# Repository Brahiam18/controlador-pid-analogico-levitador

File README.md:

# Controlador PID analógico para levitación electromagnética

-brightgreen)

Diseño, cálculo, simulación, implementación y pruebas de un controlador **PID 100 % analógico**, construido solo con amplificadores operacionales LM741, para estabilizar la posición de un objeto en levitación por atracción electromagnética. El repositorio incluye el informe técnico completo (PDF y código fuente LaTeX), las figuras, la lista de materiales, las mediciones del montaje físico y su comparación con la teoría.

> **TL;DR (EN):** Fully analog, parallel PID controller built with LM741 op-amps for an electromagnetic levitation system: error amplifier, P / I (with anti-windup leak) / D (with high-frequency limiting) stages, and a summing stage with offset that produces a 1–3 V control signal. Reference voltages are generated by resistive dividers isolated with voltage-follower buffers. Includes hand calculations, Proteus simulation and an IEEE-style report written in LaTeX (Spanish).

📄 **Informe:** [`informe/Informe_PID_Analogico_Levitador.pdf`](informe/Informe_PID_Analogico_Levitador.pdf)

---

## Resumen del diseño

| Parámetro | Valor |
|---|---|
| Topología | PID en **paralelo** (P, I y D independientes; no en cascada) |
| Amplificadores | 7 × LM741 (U1–U7) |
| Alimentación de diseño | ±16 V |
| Salida del controlador | 1 V a 3 V (1 V = error nulo) |
| Referencia de posición | `V_ref` ≈ 2 V |
| Ganancias finales | `Kp = 2.2` · `Ki,max = 4.5` · `Kd,max = 22` |
| Frecuencias de diseño | integrador: `f_aw ≈ 0.2 Hz` · derivador: `f_c ≈ 150 Hz` |

**¿Por qué un PID?** Un levitador por atracción es inestable en lazo abierto (teorema de Earnshaw). Se descartaron el control todo-o-nada (fuerza discontinua), el P puro y el PD (ambos dejan error de estado estable o no lo eliminan) y se eligió el PID: P corrige el error instantáneo, I elimina el error de estado estable y D aporta el amortiguamiento que el sistema no tiene por sí mismo.

## Arquitectura

```mermaid
flowchart LR
    S["Sensor de posición<br/>V_sensor"] --> D["Diferenciador de error<br/>U1"]
    VR["Divisor + buffer V_ref<br/>R12, R13, U6"] --> D
    D -- "V_e" --> P["Proporcional<br/>U2 (Pot1, R5)"]
    D -- "V_e" --> I["Integral + anti-windup<br/>U3 (Pot2, Ci, R11)"]
    D -- "V_e" --> De["Derivativo + filtro<br/>U4 (R6, C2, Pot3)"]
    P --> SUM["Sumador<br/>U5 (R7–R10, R_offset)"]
    I --> SUM
    De --> SUM
    VO["Divisor + buffer V_off<br/>R14, R15, U7"] --> SUM
    SUM -- "1 a 3 V" --> OUT["Etapa de potencia y bobina"]
    OUT --> OBJ["Posición del objeto"]
    OBJ -. "realimentación" .-> S
```

| Etapa | CI | Ecuación de diseño | Valores finales |
|---|---|---|---|
| Diferenciador de error | U1 | `V_e = (R2/R1)·(V_sensor − V_ref)`, `Av = 1` | R1 = R2 = R3 = R4 = 10 kΩ |
| Proporcional (P) | U2 | `V_P = −(Pot1/R5)·V_e` | R5 = 10 kΩ, Pot1 = 22 kΩ (`Kp = 2.2`) |
| Integral (I) | U3 | `V_I = −(1/(Pot2·Ci))∫V_e dt`, con fuga `R11 ‖ Ci`: `K_max = R11/Pot2` | Pot2 = 220 kΩ, Ci = 1 µF, R11 = 1 MΩ (`K_max = 4.5`) |
| Derivativo (D) | U4 | `V_D = −Pot3·C2·dV_e/dt`, `G_max = Pot3/R6`, `f_c = 1/(2π·R6·C2)` | R6 = 1 kΩ, C2 = 1 µF, Pot3 = 22 kΩ (`Kd,max = 22`) |
| Sumador | U5 | `V_PID = −(R10/R7·V_P + R10/R8·V_I + R10/R9·V_D + R10/R_offset·V_off)` | R7 = R8 = R9 = R_offset = 10 kΩ, R10 = 1 kΩ (ganancia 0.1 por rama) |
| Referencia `V_ref` | U6 | divisor + seguidor | R12 = 160 kΩ, R13 = 240 kΩ (desde 5 V → 2 V) |
| Offset `V_off` | U7 | divisor + seguidor | R14 = 96 kΩ (calculada; **pendiente de medir**), R15 = 160 kΩ |

La nomenclatura de las resistencias fue actualizada respecto a la primera versión del informe; la tabla de equivalencias está en [`docs/nomenclatura.md`](docs/nomenclatura.md).

## Problemas encontrados y cómo se resolvieron

1. **Saturación del sumador.** Con ganancia unitaria por rama, la salida teórica ante error máximo era de 23.24 V, muy por encima de los rieles. Se bajó la ganancia por rama a 0.1 (`R10`: 10 kΩ → 1 kΩ), se agregó un voltaje de offset para fijar el piso en 1 V y se redujo `Kp` de 3 a 2.2 para que el máximo converja a ≈ 3 V (3.02 V).
2. **Topología del integrador.** La resistencia de anti-windup se había conectado *en serie* con el capacitor, dejando la realimentación abierta en continua. Al colocarla en **paralelo** (`R11 ‖ Ci`) el integrador recuperó su comportamiento (salida nula para error nulo, rampa ante un escalón). Además se rediseñó `Ki` (ganancia DC máxima de 80 → 4.5) porque la original saturaba ante errores pequeños.
3. **Efecto de carga en los divisores.** Los divisores de `V_ref` y `V_off` entregaban menos voltaje del calculado al conectarse a la etapa siguiente. Se intercaló un seguidor de voltaje (U6 y U7) en cada uno.

## Placa de circuito impreso (2 PID con etapa de potencia por tarjeta)

En [`hardware/pcb/`](hardware/pcb/) hay una placa de una sola cara (170.2 × 116.8 mm, cabe en una baquela de 20 × 20 cm) con **dos controladores PID independientes, cada uno con su etapa de potencia** (TIP122, banco de sensado de 3 × 1 Ω y bornes de bobina). Para los cuatro controladores se hacen **dos tarjetas iguales**. Está lista para quemar en baquela: archivos EAGLE para Fusion, hojas de cobre espejado a escala 1:1 y de ensamble con los nombres de cada pieza (U1 a U8 sobre los TL074CN), lista de puentes y el generador en Python. El informe todavía describe el diseño con LM741.

## Etapa de potencia (convertidor tensión-corriente)

La salida del PID (`V_PID`, 1 V a 3 V) no mueve la bobina directamente: pasa por un **convertidor tensión-corriente** con un amplificador operacional (U8) y un transistor Darlington TIP122, de modo que la bobina recibe una **corriente proporcional a `V_PID`** y no depende de su resistencia ni de la fuente (mientras el transistor no se sature). Es lo que se necesita en un levitador: la fuerza magnética depende de la corriente.

**Cómo funciona.**

1. `V_PID` llega a la entrada no inversora de U8 por `R17` (10 kΩ), el potenciómetro de calibración `POT4` (10 kΩ) y `R16` (270 Ω); `POT4` fija cuántos amperios se obtienen por voltio de `V_PID`.
2. U8 maneja la base del TIP122 a través de `R_BASE` (270 Ω) y del diodo `D2` (1N4148).
3. La corriente de la bobina pasa por el TIP122 y por el **banco de sensado** (3 × 1 Ω / 5 W en paralelo = 0.33 Ω), cuya caída `V_ISENSE = 0.33 V/A · I` vuelve a la entrada inversora de U8 por `R18` (1 kΩ).
4. U8 corrige la base hasta que `V_ISENSE` iguala la tensión de su entrada no inversora; por eso `I ≈ V₊ / R_sense`, es decir, **la corriente sigue a `V_PID`**.
5. `D1` (1N5408) en antiparalelo con la bobina absorbe la tensión inducida cuando se corta la corriente. `C3` (10 nF, opcional) compensa el lazo de U8 si oscila.

| Elemento | Valor | Función |
|---|---|---|
| `R17` | 10 kΩ | entrada del convertidor desde `V_PID` |
| `POT4` | 10 kΩ | calibración (A por voltio de `V_PID`) |
| `R16` | 270 Ω | protección de la entrada no inversora de U8 |
| `R18` | 1 kΩ | realimentación de `V_ISENSE` a la entrada inversora |
| `R_BASE` | 270 Ω | limita la corriente de base del TIP122 |
| `R_sense` | 3 × 1 Ω / 5 W (0.33 Ω) | sensado de la corriente de la bobina |
| `D1` / `D2` | 1N5408 / 1N4148 | protección de la bobina / protección de la base |
| TIP122 | Darlington NPN | elemento de paso (≈ 4.7 W con 1 A: lleva disipador de ≤ 10 °C/W y tab aislado) |

**Simulación (Proteus).** El archivo [`simulacion/proteus/EtapaPID1.pdsprj`](simulacion/proteus/EtapaPID1.pdsprj) contiene el PID completo con esta etapa. La captura muestra una **variante de simulación** para comprobar el principio: LM741 como U8, resistencia de sensado de 1 Ω / 10 W, bobina de 6 Ω y fuente de 24 V. Con `V₊ = 3.015 V` la corriente por el TIP122 es de **3.014 A**, igual a `V₊ / 1 Ω`: el convertidor entrega la corriente que se le pide. En el montaje real el sensado es de 0.33 Ω, la bobina ronda los 4 Ω y la corriente de trabajo es de unos 1 A, alimentada desde módulos reductores (ver [`docs/estado_del_proyecto.md`](docs/estado_del_proyecto.md)).

## Simulación en Proteus

Cada etapa se simuló y midió con voltímetros virtuales antes del montaje. El proyecto de Proteus se encuentra en [`simulacion/proteus/`](simulacion/proteus/) (`EtapaPID1.pdsprj`). El esquemático completo está en [`informe/figuras/proteus_circuito_completo.png`](informe/figuras/proteus_circuito_completo.png) y el esquemático hecho a mano en [`informe/figuras/circuito_manuscrito.jpeg`](informe/figuras/circuito_manuscrito.jpeg).

## Resultados experimentales

Voltaje teórico vs. práctico por etapa, para error mínimo, medio y máximo (`V_sensor` = 0, 2 y 5 V con `V_ref` = 2 V). Las mediciones se tomaron con multímetro sobre el montaje en protoboard alimentado a ±16 V. Los datos completos, con error absoluto y relativo, están en [`datos/mediciones_practicas.csv`](datos/mediciones_practicas.csv).

| Etapa | Teórico mín. (V) | Teórico medio (V) | Teórico máx. (V) | Práctico mín. (V) | Práctico medio (V) | Práctico máx. (V) |
|---|---:|---:|---:|---:|---:|---:|
| Diferenciador | −2 | 0 | 3 | −2.02 | 0 | 2.99 |
| Proporcional (P) | 4.38 | −0.01 | −6.6 | 4.46 | −0.15 | −6.6 |
| Integral (I) | 9.14 | 0.07 | −13.5 | 6.22 | −0.32 | −13.22 |
| Derivativo (D) | −3.24 mV | −3.24 mV | −3.3 mV | 3 mV | 3 mV | 172 mV |
| Sumador | −0.35 | 1 | 3.01 | −0.04 | 1 | 2.96 |
| Divisor `V_ref` | 2 | 2 | 2 | 2 | 2 | 2 |
| Divisor `V_off` | −10.1 | −10.1 | −10.1 | −10.21 | −10.21 | −10.21 |

**Lectura rápida:**
- El diferenciador, el proporcional, el sumador y los divisores con buffer coinciden con lo calculado (error relativo ≤ 2 % donde el valor teórico es mayor que 0.5 V). La salida del sumador con error máximo es 2.96 V, dentro del rango de diseño de 1 V a 3 V, y con error medio es exactamente 1 V.
- La etapa integral con error mínimo da 6.22 V frente a 9.14 V teóricos (−32 %). Con ese valor práctico, el sumador resulta en −0.04 V, que es coherente con la salida medida.
- En la etapa derivativa, con entrada en DC, los valores son del orden de milivoltios; el de 172 mV con error máximo queda pendiente de analizar.

### Montaje físico

| Circuito en protoboard | Medición a la salida del diferenciador (2.99 V) |
|:-:|:-:|
|  |  |

## Simulación del campo y póster

Modelo del campo magnético de las 4 bobinas y del imán (aproximación de dipolos, solvers propios en Python, no FEMM) para estimar la corriente de equilibrio: unos **0,7 A por bobina a 30 mm** (±15 %). Es una estimación ilustrativa; **la levitación todavía no se ha logrado en el montaje**.

<p align="center">
  
</p>

- Video (720p): [`docs/simulacion_campo/campo_levitador_720p.mp4`](docs/simulacion_campo/campo_levitador_720p.mp4)
- Visor interactivo 3D: [`docs/simulacion_campo/campo_levitador.html`](docs/simulacion_campo/campo_levitador.html) (descargar y abrir en el navegador)
- Notas del modelo: [`docs/simulacion_campo/README.md`](docs/simulacion_campo/README.md)
- Póster presentado en METIE 2026: [PDF](docs/poster_metie/Poster_Levitador_METIE.pdf) · [PPTX](docs/poster_metie/Poster_Levitador_METIE.pptx)

<p align="center">
  
</p>

## Estructura del repositorio

```text
.
├── informe/
│   ├── informe_pid_analogico.tex        # código fuente del informe (IEEEtran)
│   ├── Informe_PID_Analogico_Levitador.pdf
│   └── figuras/                         # esquemáticos (incl. Proteus de la etapa de potencia), cálculos a mano y diagrama de bloques
│       └── pruebas/                     # fotografías del montaje y de las mediciones
├── docs/
│   ├── nomenclatura.md                  # nomenclatura vigente y equivalencias con la versión anterior
│   ├── errata-y-pendientes.md           # inconsistencias detectadas en el informe y tareas abiertas
│   ├── estado_del_proyecto.md           # estado actual, qué falta y requisitos de alimentación
│   ├── plan_2027.md                     # plan para lograr la levitación estable
│   ├── guia_depuracion.md               # diagnósticos y pruebas de un PID
│   ├── resumen_para_posgrado.md         # resumen del proyecto (ES/EN)
│   ├── simulacion_campo/                # visualización interactiva del campo y video
│   └── poster_metie/                    # póster de la muestra METIE 2026
├── hardware/
│   ├── lista_de_materiales.md
│   ├── lista_de_materiales.csv
│   └── pcb/                             # placa de 2 PID: .sch/.brd (Fusion/EAGLE), PDF de cobre y ensamble, generador
├── simulacion/
│   └── proteus/                         # proyecto de Proteus (PID + etapa de potencia)
├── pruebas/
│   ├── montaje/                         # fotos del montaje de los 4 PID con la base 3D (nov. 2026)
│   └── levitacion/                      # fotos de los 4 PID levitando y Vref por altura (pendiente)
├── datos/
│   └── mediciones_practicas.csv         # teórico vs. práctico, con error absoluto y relativo
├── fuente/                              # fuente ±16 V (1,5 A) / +5 V de los 4 PID (informe, esquemáticos, simulación, PCB, pruebas)
├── LICENSE
└── README.md
```

## Compilar el informe

Requiere una distribución de TeX Live con `IEEEtran`, `siunitx` y `booktabs`.

```bash
cd informe
latexmk -pdf informe_pid_analogico.tex
```

## Estado y próximos pasos

**Noviembre de 2026:** los 4 PID, la etapa de potencia y la base impresa en 3D están montados y funcionando por separado, pero la levitación estable a 3 cm quedó pendiente: falta un método rápido para fijar los `V_ref` y los sensores ven una variación muy pequeña del campo. El trabajo continúa en 2027; ver [`docs/estado_del_proyecto.md`](docs/estado_del_proyecto.md), [`docs/plan_2027.md`](docs/plan_2027.md) y [`docs/guia_depuracion.md`](docs/guia_depuracion.md).

- [x] Diseño y cálculo de cada etapa
- [x] Simulación en Proteus
- [x] Informe técnico en LaTeX (formato IEEE)
- [ ] Medir `R14` (divisor de `V_off`) y registrar su valor final
- [x] Tomas de voltaje prácticas por etapa (error mínimo, medio y máximo)
- [x] Fotografías del montaje
- [ ] Analizar la desviación de la etapa integral con error mínimo y el valor de la etapa derivativa con error máximo
- [ ] Capturas de osciloscopio con la escala legible (pruebas con señal senoidal)
- [x] Agregar el archivo del proyecto de Proteus
- [x] Documentar la etapa de potencia (README e informe)
- [ ] Fotos de los 4 PID con el objeto levitando y `V_ref` por altura ([`pruebas/levitacion/`](pruebas/levitacion/))
- [ ] Aplicar la [errata](docs/errata-y-pendientes.md) al informe (versión 1.1)

## Autor

**Brahiam Alberto Campiño Romero**: Ingeniería Electrónica, Universidad de Ibagué (Ibagué-Tolima, Colombia) · [@Brahiam18](https://github.com/Brahiam18)

## Licencia

[MIT](LICENSE)

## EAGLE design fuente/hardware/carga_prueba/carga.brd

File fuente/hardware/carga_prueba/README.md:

# Placa de la carga de prueba R_L (10 Ω / 20 Ω)

Placa de **una cara** de **95 × 95 mm** para las 4 resistencias de cemento de **10 Ω / 10 W** de la carga de prueba. No uses la protoboard para esto: sus contactos aguantan alrededor de 1 A y las resistencias pasan de 150 °C.

## Circuito
(R1 + R2) ‖ (R3 + R4). **JP1** es una bornera de 2 vías que elige la carga:

| JP1 | Resistencia | Corriente con 16 V | Potencia en cada resistencia |
|---|---|---|---|
| **Puenteado** (alambre de 18 AWG o interruptor de 3 A) | 10 Ω | **1,6 A** (corriente completa) | 6,4 W |
| **Abierto** | 20 Ω (solo R1 + R2) | **0,8 A** (media corriente) | 6,4 W en R1 y R2; R3 y R4 frías |

**J1** (bornera de 2 vías) va con un cable de 18 AWG a **J4** (+16 V / GND) o a **J5** (−16 V / GND) de la fuente. La polaridad no importa.

## Archivos
| Archivo | Para qué sirve |
|---|---|
| `cobre_espejado_1a1.pdf` | Cara de cobre espejada a 1:1 para planchar (la regla debe medir 50 mm) |
| `ensamble_1a1.pdf` | Lado de componentes a 1:1 |
| `carga.sch`, `carga.brd` | Formato EAGLE para Fusion (cargar los dos juntos) |
| `generar.py` | Genera todo lo anterior (`python3 generar.py`) |

## Reglas y montaje
- Pistas de 2,5 mm con quiebres a 45°; separación mínima entre redes de 1,75 mm; ninguna pista a menos de 2 mm del borde.
- Pads de 3,2 mm con taladro de 1,2 mm para las patas de las resistencias (55,88 mm entre agujeros) y de 1,3 mm para las borneras.
- **Monta las resistencias levantadas 5–10 mm** de la placa, con las patas dobladas en ángulo recto. Quedan separadas unos 9 mm entre sí para que se ventilen.
- Estaña las pistas.
- Pon separadores M3 en los 4 agujeros para que la placa no quede apoyada sobre la mesa.
- **No las toques durante la prueba** y espera a que se enfríen antes de cambiar el puente.

## Materiales
| Cant. | Pieza |
|---|---|
| 4 | Resistencia de cemento 10 Ω / 10 W |
| 2 | Bornera de tornillo 2 vías, paso 5,08 mm (J1, JP1) |
| 1 | Baquela una cara 10 × 10 cm |
| 4 | Separadores M3 de 10 mm con tornillo |
| — | Cable de 18 AWG para la conexión a la fuente y para el puente de JP1 |

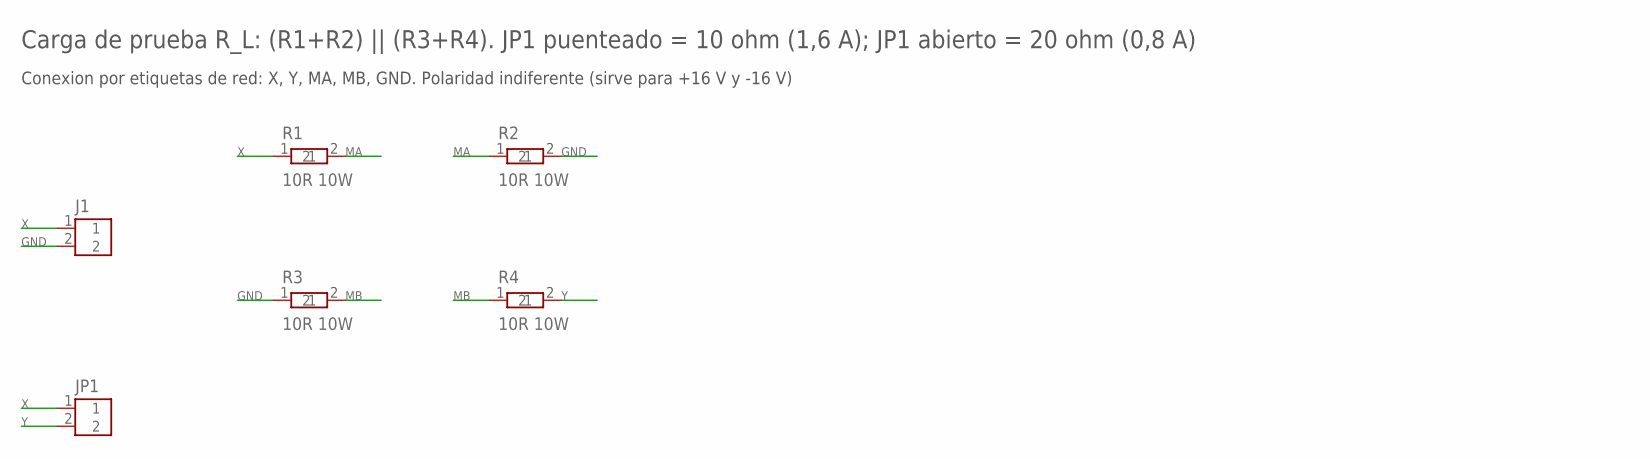
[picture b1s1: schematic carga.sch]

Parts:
J1: A J4 o J5; TERM2
JP1: SEL 10/20R; TERM2
R1, R2, R3, R4: 10R 10W; R10W

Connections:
GND: J1.2, R2.2, R3.1
MA: R1.2, R2.1
MB: R3.2, R4.1
X: J1.1, JP1.1, R1.1
Y: JP1.2, R4.2

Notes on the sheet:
Carga de prueba R_L: (R1+R2) || (R3+R4). JP1 puenteado = 10 ohm (1,6 A); JP1 abierto = 20 ohm (0,8 A)
Conexion por etiquetas de red: X, Y, MA, MB, GND. Polaridad indiferente (sirve para +16 V y -16 V)

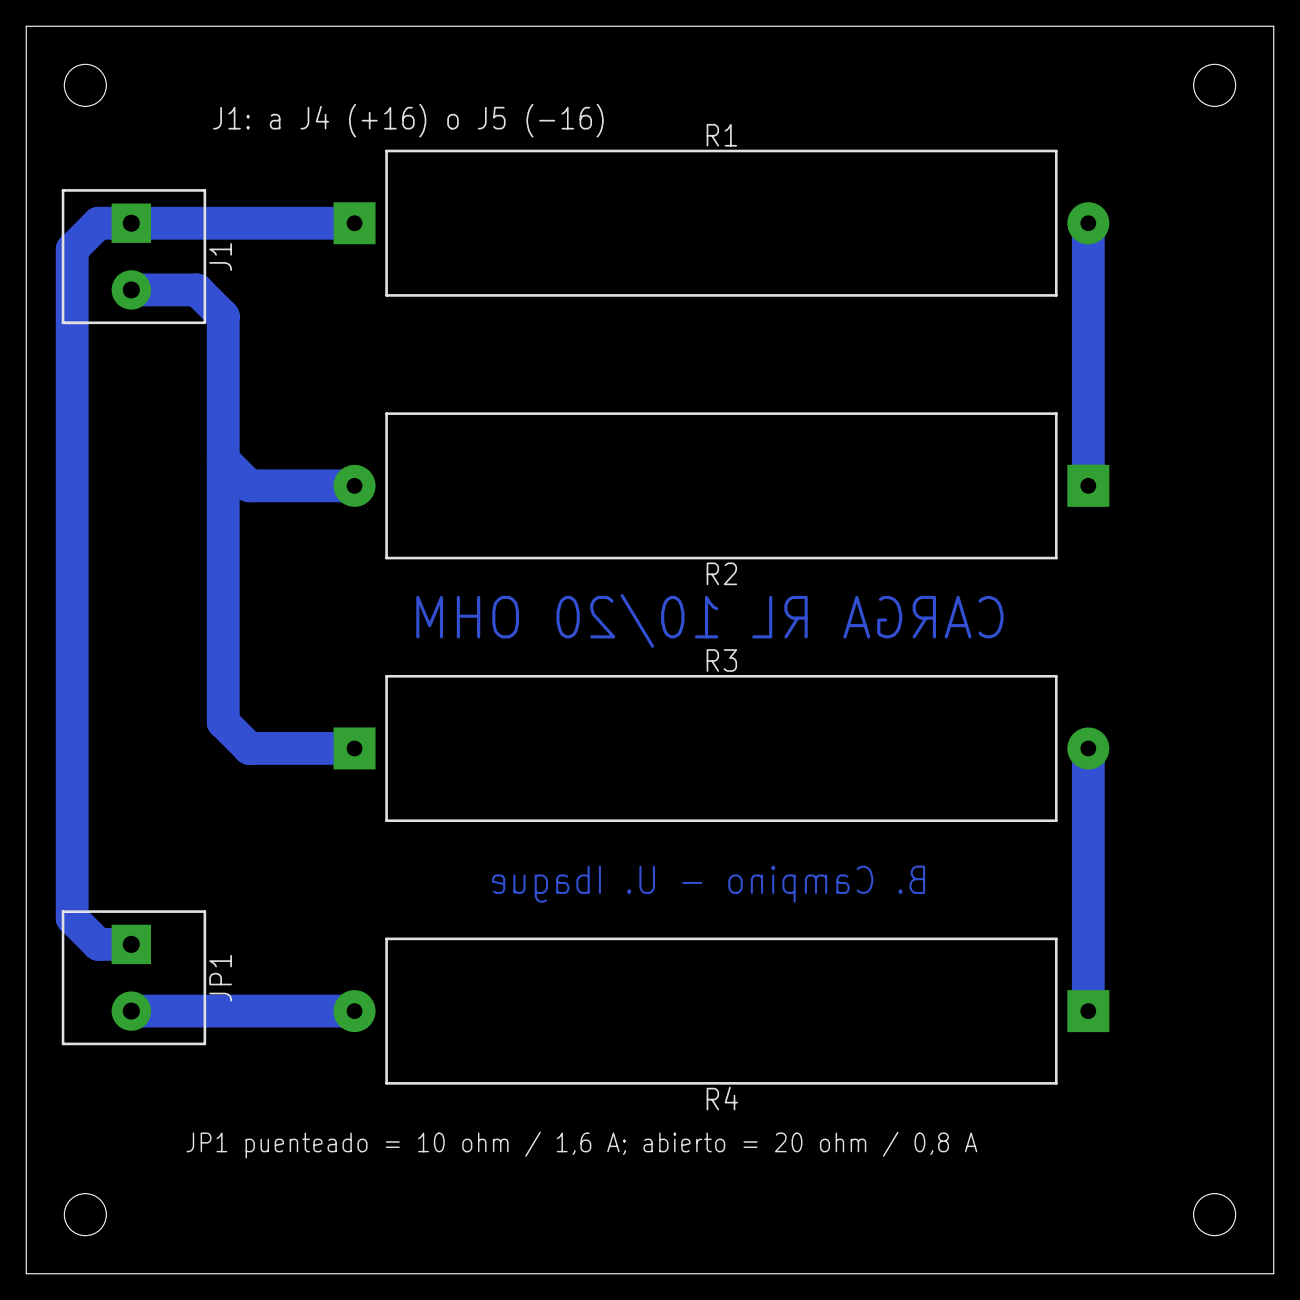
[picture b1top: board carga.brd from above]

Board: 2 copper layers, 95.0 x 95.0 mm, 6 parts (0 on the bottom side), 5 nets.

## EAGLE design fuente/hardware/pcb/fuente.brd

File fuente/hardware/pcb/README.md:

# Placa de la fuente ±16 V / 1,6 A y +5 V (versión 2.2)

Placa de **una sola cara** (cobre inferior) de **190,5 × 139,7 mm**, que cabe en una baquela de 20 × 15 cm. Se fabrica por transferencia de tóner o con película fotosensible. Lleva **8 puentes de alambre** (P1–P8) del lado de componentes, todos en redes de señal o de baja corriente. Pistas biseladas a 45° y salida J2 hecha con dos borneras de 2 vías (J2A y J2B).

**Cambios de la v2.2:** R7 y R15 son ahora **dos huellas de 1 W cada una** (R7A ‖ R7B y R15A ‖ R15B) para montar 2 × 5,6 Ω en paralelo (= 2,8 Ω). Si consigues la de 2,7 Ω / 1 W, monta solo R7A y R15A y deja R7B y R15B vacías. Además hay **15 puntos de prueba** (TP1–TP15) para el multímetro; para hacerles sitio la placa se recolocó y se ruteó de nuevo.

| Archivo | Para qué sirve |
|---|---|
| `fuente.sch` y `fuente.brd` | Esquemático y placa en formato EAGLE. En Fusion: *Cargar* los dos archivos juntos con "Crear diseño de la electrónica" marcado. Las piezas están en la biblioteca propia `fuente16`. El esquemático conecta por **etiquetas de red**; el dibujo legible está en `../../esquematicos/` |
| `cobre_espejado_1a1.pdf` | Cara de cobre **espejada** a escala 1:1, para planchar o insolar |
| `ensamble_1a1.pdf` | Página 1: lado de componentes a 1:1 (referencias, pin 1, puentes en rojo). Página 2: vista ampliada con referencia y valor |
| `puentes.md` | Lista de los 8 puentes con red, longitud y extremos |
| `generador/` | Código en Python que hace la colocación, el ruteo, la verificación y la exportación (`NO_TP=1 python3 buscar.py 3 placa.json`, luego `python3 incremental.py placa.json placa.json` para agregar los puntos de prueba y `python3 build.py placa.json ..`) |

## Reglas de diseño (verificadas por `verify.py` y `xmlcheck.py`)
- Pistas de 0,8 mm. Las redes de corriente alta (secundario `ACA`/`ACB`/`AC1`/`AC2`, `VRAWP`, `VRAWN`, `E1`, `E2`, `VA1`, `VA2`, `+16V`, `-16V`, `GND`) van en 1,6 mm.
- Pads de 2,0 mm, y de 2,6 mm en borneras, portafusibles, 1N5408, R_SC (5 W) y condensadores grandes.
- Taladros de 0,9 a 1,3 mm según la pieza (C1 de 15 000 µF: Ø ≤ 35 mm, 10 mm entre patas; C2A/C2B de 6800 µF: Ø 28 mm, 10 mm entre patas) y 3,2 mm para los 4 agujeros de montaje.
- Separación mínima entre cobres de redes distintas: regla de **0,40 mm**; en la placa final es de **0,59 mm**, medida sobre la geometría final.
- Ninguna pista a menos de 1 mm del borde y ningún puente a menos de 3 mm del borde de los disipadores.
- **Pistas a 45°**: las 234 esquinas de las pistas están biseladas (sin ángulos rectos), lo que mejora el grabado y reparte mejor la corriente. Solo quedan a 90° las uniones en T y los quiebres sobre un pad.
- Las 32 redes están completas, sin cortos, y el `.sch` y el `.brd` son consistentes.

## Fabricación
1. Imprimir `cobre_espejado_1a1.pdf` **sin escalar** ("tamaño real"). La regla de abajo debe medir 50 mm.
2. Transferir, atacar con cloruro férrico y taladrar. El punto blanco de cada pad marca el centro.
3. Estañar las pistas anchas (secundario, V_RAW, ±16 V y GND) para que soporten mejor los 1,6 A.
4. Revisar con el multímetro, antes de soldar, que no haya cortos: `+16V`–`GND`, `-16V`–`GND`, `+5V`–`GND`, `VRAWP`–`GND`, `VRAWN`–`GND` y `+16V`–`-16V`.
5. Soldar en este orden: primero los puentes (alambre aislado, calibre 22 AWG o más grueso), luego resistencias y diodos, después TO‑92, trimmers, condensadores pequeños, LED, borneras, portafusibles, C1, C2A y C2B, y al final los TO‑220/TO‑126 ya atornillados a su disipador.

## Puntos de prueba (TP1–TP15)
Pads rojos con el nombre de la red en `ensamble_1a1.pdf`. Punta negra del multímetro en **TP13, TP14 o TP15 (GND)**. Si quieres enganchar caimanes, suelda en cada pad un alambre 22 AWG doblado en U.

| TP | Red | Qué mides |
|---|---|---|
| TP1 / TP6 | V_RAW+ / V_RAW− | Salida del filtro: ±25 a ±28 V sin carga, ±23 a ±24 V con R_L |
| TP2 / TP7 | E1 / E2 | Después de R_SC: **corriente del riel** = (TP1 − TP2)/0,27 Ω (0,43 V ↔ 1,6 A) |
| TP3 / TP8 | V_A1 / V_A2 | Salida del limitador (colector del Darlington) |
| TP4 / TP9 | IN1 / IN2 | Entrada del regulador; TP4 − TP5 ≥ 2 V para que regule |
| TP5 / TP10 | +16 V / −16 V | Salidas (ajuste con RV1 / RV2) |
| TP11 / TP12 | V_IN5 / +5 V | Entrada (≈ 10 V) y salida (5,00 V, RV3) del regulador de +5 V |
| TP13–TP15 | GND | Referencia |

## Disipadores (importante)
- **Q1 (TIP42C), Q2 (BD140), Q4 (TIP42C) y U1 (LM317T)** van en el borde superior; **Q5 (TIP41C), Q6 (BD139), Q8 (TIP41C) y U2 (LM337T)** en el inferior. Cada grupo comparte un disipador de **≤ 2 °C/W** (por ejemplo un perfil aletado de unos 100 × 60 × 30 mm) que sobresale del borde de la placa.
- La aleta de cada pieza está conectada eléctricamente a uno de sus pines. Por eso **cada pieza lleva mica (o silicona) y buje aislante**. Después de montarlas, comprobar con el óhmetro que entre cada aleta y el disipador haya circuito abierto.
- **U3** (+5 V) disipa unos 0,3 W y no necesita disipador.

## Guía de conexión

| Desde | Hacia | Nota |
|---|---|---|
| Red 115 V (L) | Fusible F1 T1 A → interruptor S1 → primario del transformador | Fuera de la placa, con los empalmes aislados |
| Red 115 V (N) | Otro extremo del primario | |
| Secundario 18‑0‑18 V: extremo A, toma central, extremo B | **J1‑1**, **J1‑2 (GND)**, **J1‑3** | F2 y F3 (T3,15 A) están en la placa |
| **J2A**‑1 +16 V, J2A‑2 −16 V, **J2B**‑1 GND, J2B‑2 +5 V (dos borneras de 2 vías encajadas) | `J_PWR` pines 1, 2, 3 y 4 de **una** tarjeta PID; la otra tarjeta se une a la primera por su `J_PWR` | Mismo orden de pines en los dos lados |
| **J4‑1 (+16 V), J4‑2 (GND)** | Carga de prueba `R_L` = 10 Ω (4 × 10 Ω / 10 W en serie‑paralelo) | **Removible**: solo durante la prueba de 1,5 A |
| **J5‑1 (−16 V), J5‑2 (GND)** | Carga de prueba `R_L` | Un riel a la vez |
| J3 (V_RAW+, GND, V_RAW−) | Osciloscopio | Medición del rizado de C1 y C2 |

**Tierras:** la tierra de esta fuente (GND) es solo de señal. La fuente de las bobinas (`VBOB`/`PGND`) va aparte. GND y PGND se unen **en un solo punto**, el puente `JP_GND` soldado en una sola de las cuatro etapas de las tarjetas PID. No unir GND y PGND en ningún otro lugar, tampoco dentro de esta fuente.

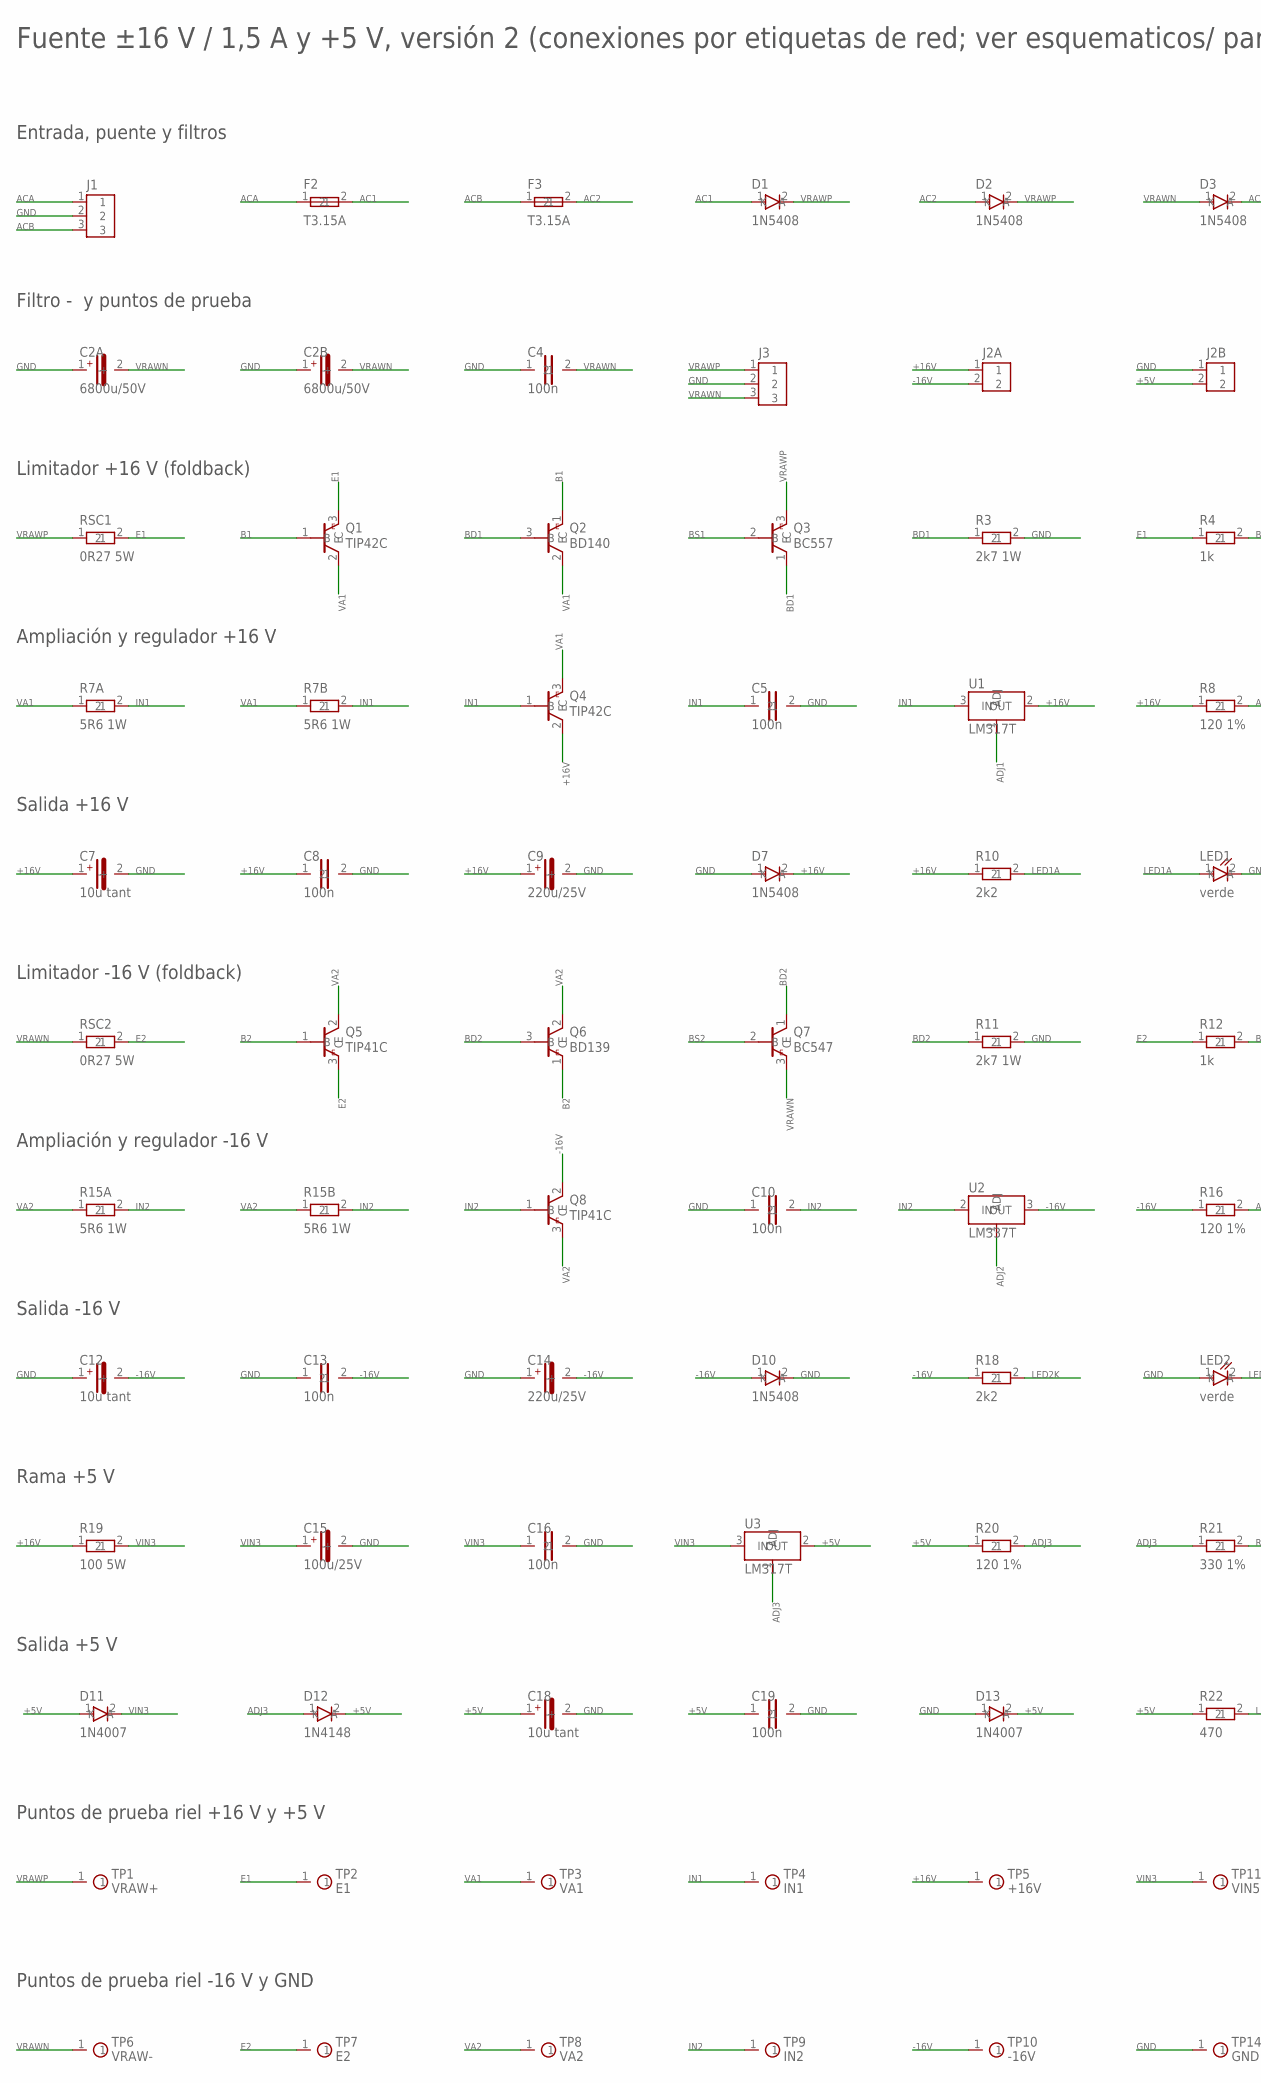
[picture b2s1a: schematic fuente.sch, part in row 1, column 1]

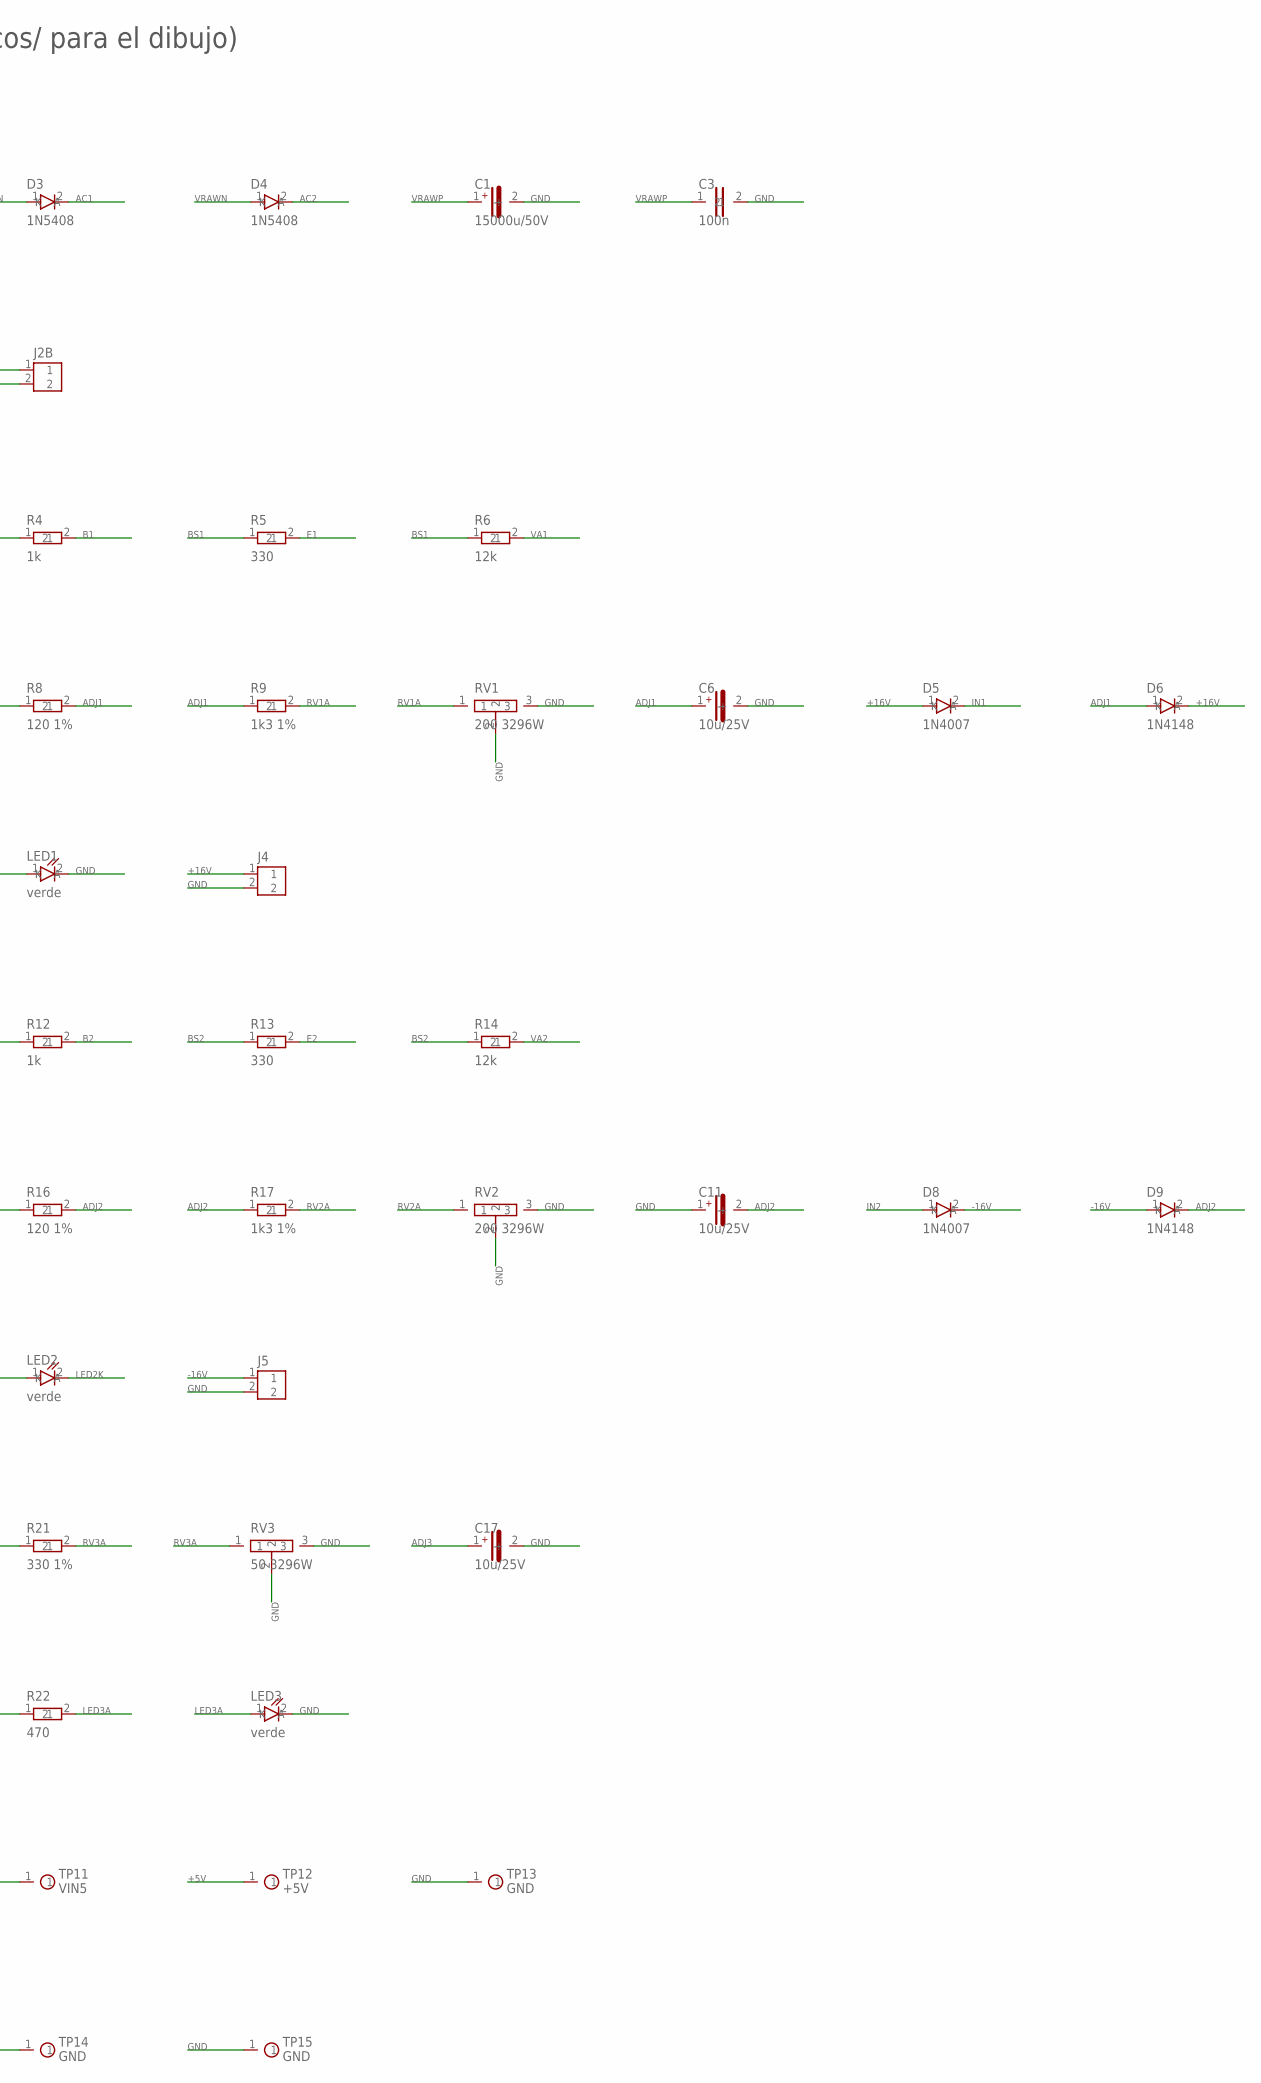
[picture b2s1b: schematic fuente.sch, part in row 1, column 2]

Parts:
C1: 15000u/50V; CPOL35
C2A, C2B: 6800u/50V; CPOL25
C3, C4, C5, C8, C10, C13, C16, C19: 100n; CAP
C6, C11, C17: 10u/25V; CPOL5
C7, C12, C18: 10u tant; CTANT
C9, C14: 220u/25V; CPOL8
C15: 100u/25V; CPOL6
D1, D2, D3, D4, D7, D10: 1N5408; DIODE
D5, D8, D11, D13: 1N4007; DO41
D6, D9, D12: 1N4148; DO35
F2, F3: T3.15A; FUSE
J1: SEC 18-0-18; TERM3
J2A: +16/-16; TERM2
J2B: GND/+5; TERM2
J3: TP; HDR3
J4: RL +16; TERM2
J5: RL -16; TERM2
LED1, LED2, LED3: verde; LED5
Q1, Q4: TIP42C; TO220
Q2: BD140; TO126
Q3: BC557; TO92
Q5, Q8: TIP41C; TO220
Q6: BD139; TO126
Q7: BC547; TO92
R3, R11: 2k7 1W; RES1W
R4, R12: 1k; RES10
R5, R13: 330; RES10
R6, R14: 12k; RES10
R7A, R7B, R15A, R15B: 5R6 1W; RES1W
R8, R16, R20: 120 1%; RES10
R9, R17: 1k3 1%; RES10
R10, R18: 2k2; RES10
R19: 100 5W; RES3W
R21: 330 1%; RES10
R22: 470; RES10
RSC1, RSC2: 0R27 5W; RES5W
RV1, RV2: 200 3296W; TRIM
RV3: 50 3296W; TRIM
TP1: VRAW+; TP
TP2: E1; TP
TP3: VA1; TP
TP4: IN1; TP
TP5: +16V; TP
TP6: VRAW-; TP
TP7: E2; TP
TP8: VA2; TP
TP9: IN2; TP
TP10: -16V; TP
TP11: VIN5; TP
TP12: +5V; TP
TP13, TP14, TP15: GND; TP
U1, U3: LM317T; TO220
U2: LM337T; TO220

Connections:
+5V: C18.1 (+), C19.1, D11.1 (A), D12.2 (K), D13.2 (K), J2B.2, R20.1, R22.1, TP12.1, U3.2 (OUT)
+16V: C7.1 (+), C8.1, C9.1 (+), D5.1 (A), D6.2 (K), D7.2 (K), J2A.1, J4.1, Q4.2 (C), R8.1, R10.1, R19.1, TP5.1, U1.2 (OUT)
-16V: C12.2 (-), C13.2, C14.2 (-), D8.2 (K), D9.1 (A), D10.1 (A), J2A.2, J5.1, Q8.2 (C), R16.1, R18.1, TP10.1, U2.3 (OUT)
AC1: D1.1 (A), D3.2 (K), F2.2
AC2: D2.1 (A), D4.2 (K), F3.2
ACA: F2.1, J1.1
ACB: F3.1, J1.3
ADJ1: C6.1 (+), D6.1 (A), R8.2, R9.1, U1.1 (ADJ)
ADJ2: C11.2 (-), D9.2 (K), R16.2, R17.1, U2.1 (ADJ)
ADJ3: C17.1 (+), D12.1 (A), R20.2, R21.1, U3.1 (ADJ)
B1: Q1.1 (B), Q2.1 (E), R4.2
B2: Q5.1 (B), Q6.1 (E), R12.2
BD1: Q2.3 (B), Q3.1 (C), R3.1
BD2: Q6.3 (B), Q7.1 (C), R11.1
BS1: Q3.2 (B), R5.1, R6.1
BS2: Q7.2 (B), R13.1, R14.1
E1: Q1.3 (E), R4.1, R5.2, RSC1.2, TP2.1
E2: Q5.3 (E), R12.1, R13.2, RSC2.2, TP7.1
GND: C1.2 (-), C2A.1 (+), C2B.1 (+), C3.2, C4.1, C5.2, C6.2 (-), C7.2 (-), C8.2, C9.2 (-), C10.1, C11.1 (+), C12.1 (+), C13.1, C14.1 (+), C15.2 (-), C16.2, C17.2 (-), C18.2 (-), C19.2, D7.1 (A), D10.2 (K), D13.1 (A), J1.2, J2B.1, J3.2, J4.2, J5.2, LED1.2 (K), LED2.1 (A), LED3.2 (K), R3.2, R11.2, RV1.2, RV1.3, RV2.2, RV2.3, RV3.2, RV3.3, TP13.1, TP14.1, TP15.1
IN1: C5.1, D5.2 (K), Q4.1 (B), R7A.2, R7B.2, TP4.1, U1.3 (IN)
IN2: C10.2, D8.1 (A), Q8.1 (B), R15A.2, R15B.2, TP9.1, U2.2 (IN)
LED1A: LED1.1 (A), R10.2
LED2K: LED2.2 (K), R18.2
LED3A: LED3.1 (A), R22.2
RV1A: R9.2, RV1.1
RV2A: R17.2, RV2.1
RV3A: R21.2, RV3.1
VA1: Q1.2 (C), Q2.2 (C), Q4.3 (E), R6.2, R7A.1, R7B.1, TP3.1
VA2: Q5.2 (C), Q6.2 (C), Q8.3 (E), R14.2, R15A.1, R15B.1, TP8.1
VIN3: C15.1 (+), C16.1, D11.2 (K), R19.2, TP11.1, U3.3 (IN)
VRAWN: C2A.2 (-), C2B.2 (-), C4.2, D3.1 (A), D4.1 (A), J3.3, Q7.3 (E), RSC2.1, TP6.1
VRAWP: C1.1 (+), C3.1, D1.2 (K), D2.2 (K), J3.1, Q3.3 (E), RSC1.1, TP1.1

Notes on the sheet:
Entrada, puente y filtros
Filtro - y puntos de prueba
Limitador +16 V (foldback)
Ampliación y regulador +16 V
Salida +16 V
Limitador -16 V (foldback)
Ampliación y regulador -16 V
Salida -16 V
Rama +5 V
Salida +5 V
Puntos de prueba riel +16 V y +5 V
Puntos de prueba riel -16 V y GND
Fuente ±16 V / 1,5 A y +5 V, versión 2 (conexiones por etiquetas de red; ver esquematicos/ para el dibujo)

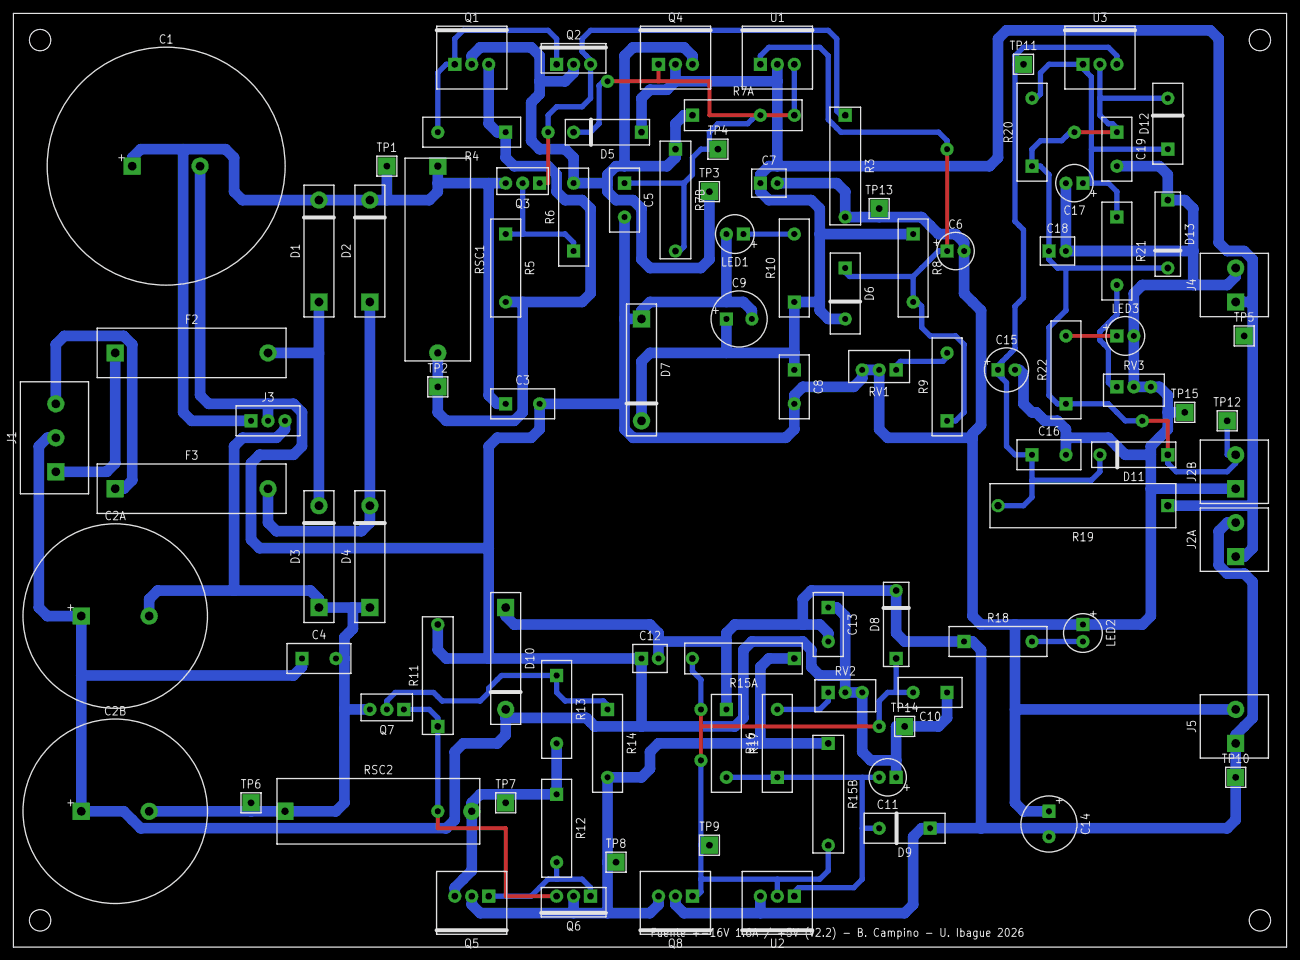
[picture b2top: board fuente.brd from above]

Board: 2 copper layers, 190.5 x 139.7 mm, 97 parts (0 on the bottom side), 32 nets.
